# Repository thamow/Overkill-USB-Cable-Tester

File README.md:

# Overkill USB Cable Tester

[Post on Reddit](https://www.reddit.com/r/PCB/comments/1lwca66/review_request_overkill_usb_tester/?utm_source=share&utm_medium=web3x&utm_name=web3xcss&utm_term=1&utm_content=share_button)

Disclaimer: Work in Progress! Do not expect the current version to work as intended!

**tl;dr:** Designed my second ever PCB and want some suggestions for potential improvements or problems / errors in my design (PCB not routed yet). See questions down below (last paragraph).

Yes, this design is complete overkill! This PCB is mostly for me to try stuff out and intentionally not cost-optimised. That said, should you see improvements without reducing the feature set, go ahead!

## Questions

Some of my most pressing questions are:

- **Will the LED Matrix work** with the two SN74HC595s? (see paragraph "Indicator LED Matrix" below)
- **How does the double mapping of Pin PA14 work?** (BOOT0 & SWCLK) What do I have to do in order to use it in either function? (-> paragraph "SWD" below)
- **Does the back-feed protection work the way I intend it to?** (-> paragraph "Power" below)
- **Is there something I should have done differently regarding the USB-C of the UART controller?** Anything wrong with the ESD protection or shield filtering I put there? (see schematic image 3)
- **Do I need series resistors on the SWD lines?** They are supposed to act as noise suppression to reduce ringing and stuff. Are they good to have or unnecessary? (see R10, R11, R12)

Again, I know the design is complete overkill but suggestions for more elegant solutions are more than welcome!

## Detailed Info

I wanted to have a USB Tester for a long time and thought instead of buying one I'd seize the opportunity to learn some things about PCB design and USB-C. As stated above, this is my second ever PCB design and I originally have a background in IT not EE so expect some rookie mistakes! What started out as a simple "put current through to light some LEDs" turned into "i definitely want cross wire and short detection and want to read out eMarkers and everything".

### Basic working principle

I have two sides: Side A (left side) and Side B (right side). If you plug in a cable (one end into each side) the tester should check which pins are connected and which aren't, which are connected even though they shouldn't and so on. I do this by applying a voltage to each pin after another on the A-Side (s. Output Drivers SN74HC595) and checking which pins get pulled high on the opposing Side B (s. Input Drivers SN74HC165).

#### Detailed working principle

Below I will go into detail on the individual sections of the schematic and my reasoning behind some things.

#### µC - STM32

The controller IC is an STM32 G071CBT6.

##### USB PD

I chose that controller specifically due to its build-in USB PD Communication Chip. I want to use it to read out the eMarkers of USB C Cables to be able to check the cables current and speed rating and potential USB Alt modes.

You may notice that I put the CC1 and CC2 lines of both side on a separate USB PD Controller as well as on ADC pins (12-15). I did this so that i could check for built-in pull-up and pull-down resistors inside the cable (which some cables must include in order to be up to spec).

##### Programming

To program the µC I implemented two methods: UART and SWD.

**SWD**

SWD itself seems to be quite simple from my understanding. I broke out the necessary pins to an appropriate connector (J1). The information I found only does however raise some questions regarding series resistors (see questions section down below).

Furthermore, the STM32 I choose uses the SWCLK pin as the BOOT0 pin as well (Alternate Mode). I could not yet find out how that is supposed to work. Therefore I opted to place a jumper (JP7) to either connect to the BOOT push button (SW4) or to the SWD connector (J1).

**UART**

Because I wanted to try it out, in addition to the SWD interface I used a serial to USB converter (U3 CH340X) to program the µC via USB and to be able to implement serial log to a PC for more detailed test reports.

Again, it was not clear to me how to connect the RST and BOOT0 pins exactly so I placed two solder jumper (JP5/6) to be able to easily change the pin mapping while testing.

#### Indicator LED Matrix

Well...the number of LEDs got a bit out of hand... So I decided to use a matrix powered by two SN74HC595 tri-state shift registers. Partly I did this to limit the number of shift registers needed but partly because I wanted to try it, which seems to be the theme of this build.

#### Power

With the external SWD and USB inputs I expanded the power circuit (which is probably a good thing should the CR2032 prove to be insufficient). The power circuit is designed around a buck converter to step down the external supply voltage (5V USB) down to 3.3V.

Since the µC will happily run with less then 2.5V so the voltage drop that will occur when feeding the buck converter with 3.3V from the SWD interface should be a non-issue but if the buck converter fail, I can still bridge that (JP3) and feed the board directly.

I implemented back-feed protection so that if external power is provided, it does not apply a potentially higher positive voltage to the battery and cuts it off. Here I wanted to avoid a voltage drop of 300mV so I used a MOSFET instead.

#### Test Points

I had that idea about the board design you can see in the images. To pull that off I designed a custom multi-part symbol and footprint.

In the fourth image you can see that I labeled the different test-points. Essentially the PCB Design doubles as test points. Each pin of the USB-C graphic in the centre of the PCB is a test point for that appropriate pin. Since each pin exists on both sides but the graphics only provides one pad per pin, I added a second test point for each pin. For example, if you would want to test for continuity between Pin B12 (upmost left pin) with a multimeter, you would test between the upper left test point left from GND label and the B12 pin inside the graphics.

Again, I tried to show this in the fourth image I hope that makes it more clear.

#### Unpopulated Parts

You may have noticed some unpopulated parts on my PCB. In the case of pull-up or down resistors those are mainly there as placeholders in case I need them but according to the datasheets I shouldn't need them.

The series resistors on the SWD lines are supposed to be noise suppression resistors? I am quite unsure if they are necessary (see question in the questions section).

And that's about it I guess!

## Improvements for the next Revision

### STM32 with USB 2.0 build in

To replace the external UART Bridge that presents a COM port for programming via USB and for serial out, a different MCU could be used with built-in USB 2.0 support instead. This has multiple advantages:

- reducing number of parts (smaller BOM)
  
- broader feature set (debugging/virtual network adapter via USB, which could be used for running a web server hosting a website https://github.com/fetisov/lrndis, https://www.youtube.com/watch?v=hsqWIqY8b6A), (it also makes web flashing possible through WebUSB https://github.com/siliconwitchery/web-stm32-updater), (of course, serial communication is also an option via CDC https://wiki.st.com/stm32mcu/wiki/Introduction_to_USB_with_STM32)

The STM32G0 series seems the be the best suited one, as it features two USB-C PD interfaces (UCPD1/2). These are used for checking for eMarkers on both USB-C receptacles (Side A and B). One could argue that only one UCPD interface is needed since eMarkers can be read out from either side of the cable. For USB-C to C and also USB-C to A cables this would work fine. The UCPD interface would be connected to the B-Side receptacle and read out any eMarker in the cable (A-Side would not work for USB-C to A cables, which are Plugged in to the B-Side Type C receptacle, not the A-Side one).

For cables like USB-C to Micro-B this would however not work.

## License

This project is licensed under the

[Creative Commons Attribution-NonCommercial-ShareAlike 4.0 International License](https://creativecommons.org/licenses/by-nc-sa/4.0/).

Copyright (c) 2025 by the original creator and author (GitHub: [thamow](https://github.com/thamow))

Attribution required. Commercial use not permitted. Derivatives must be shared under the same license.

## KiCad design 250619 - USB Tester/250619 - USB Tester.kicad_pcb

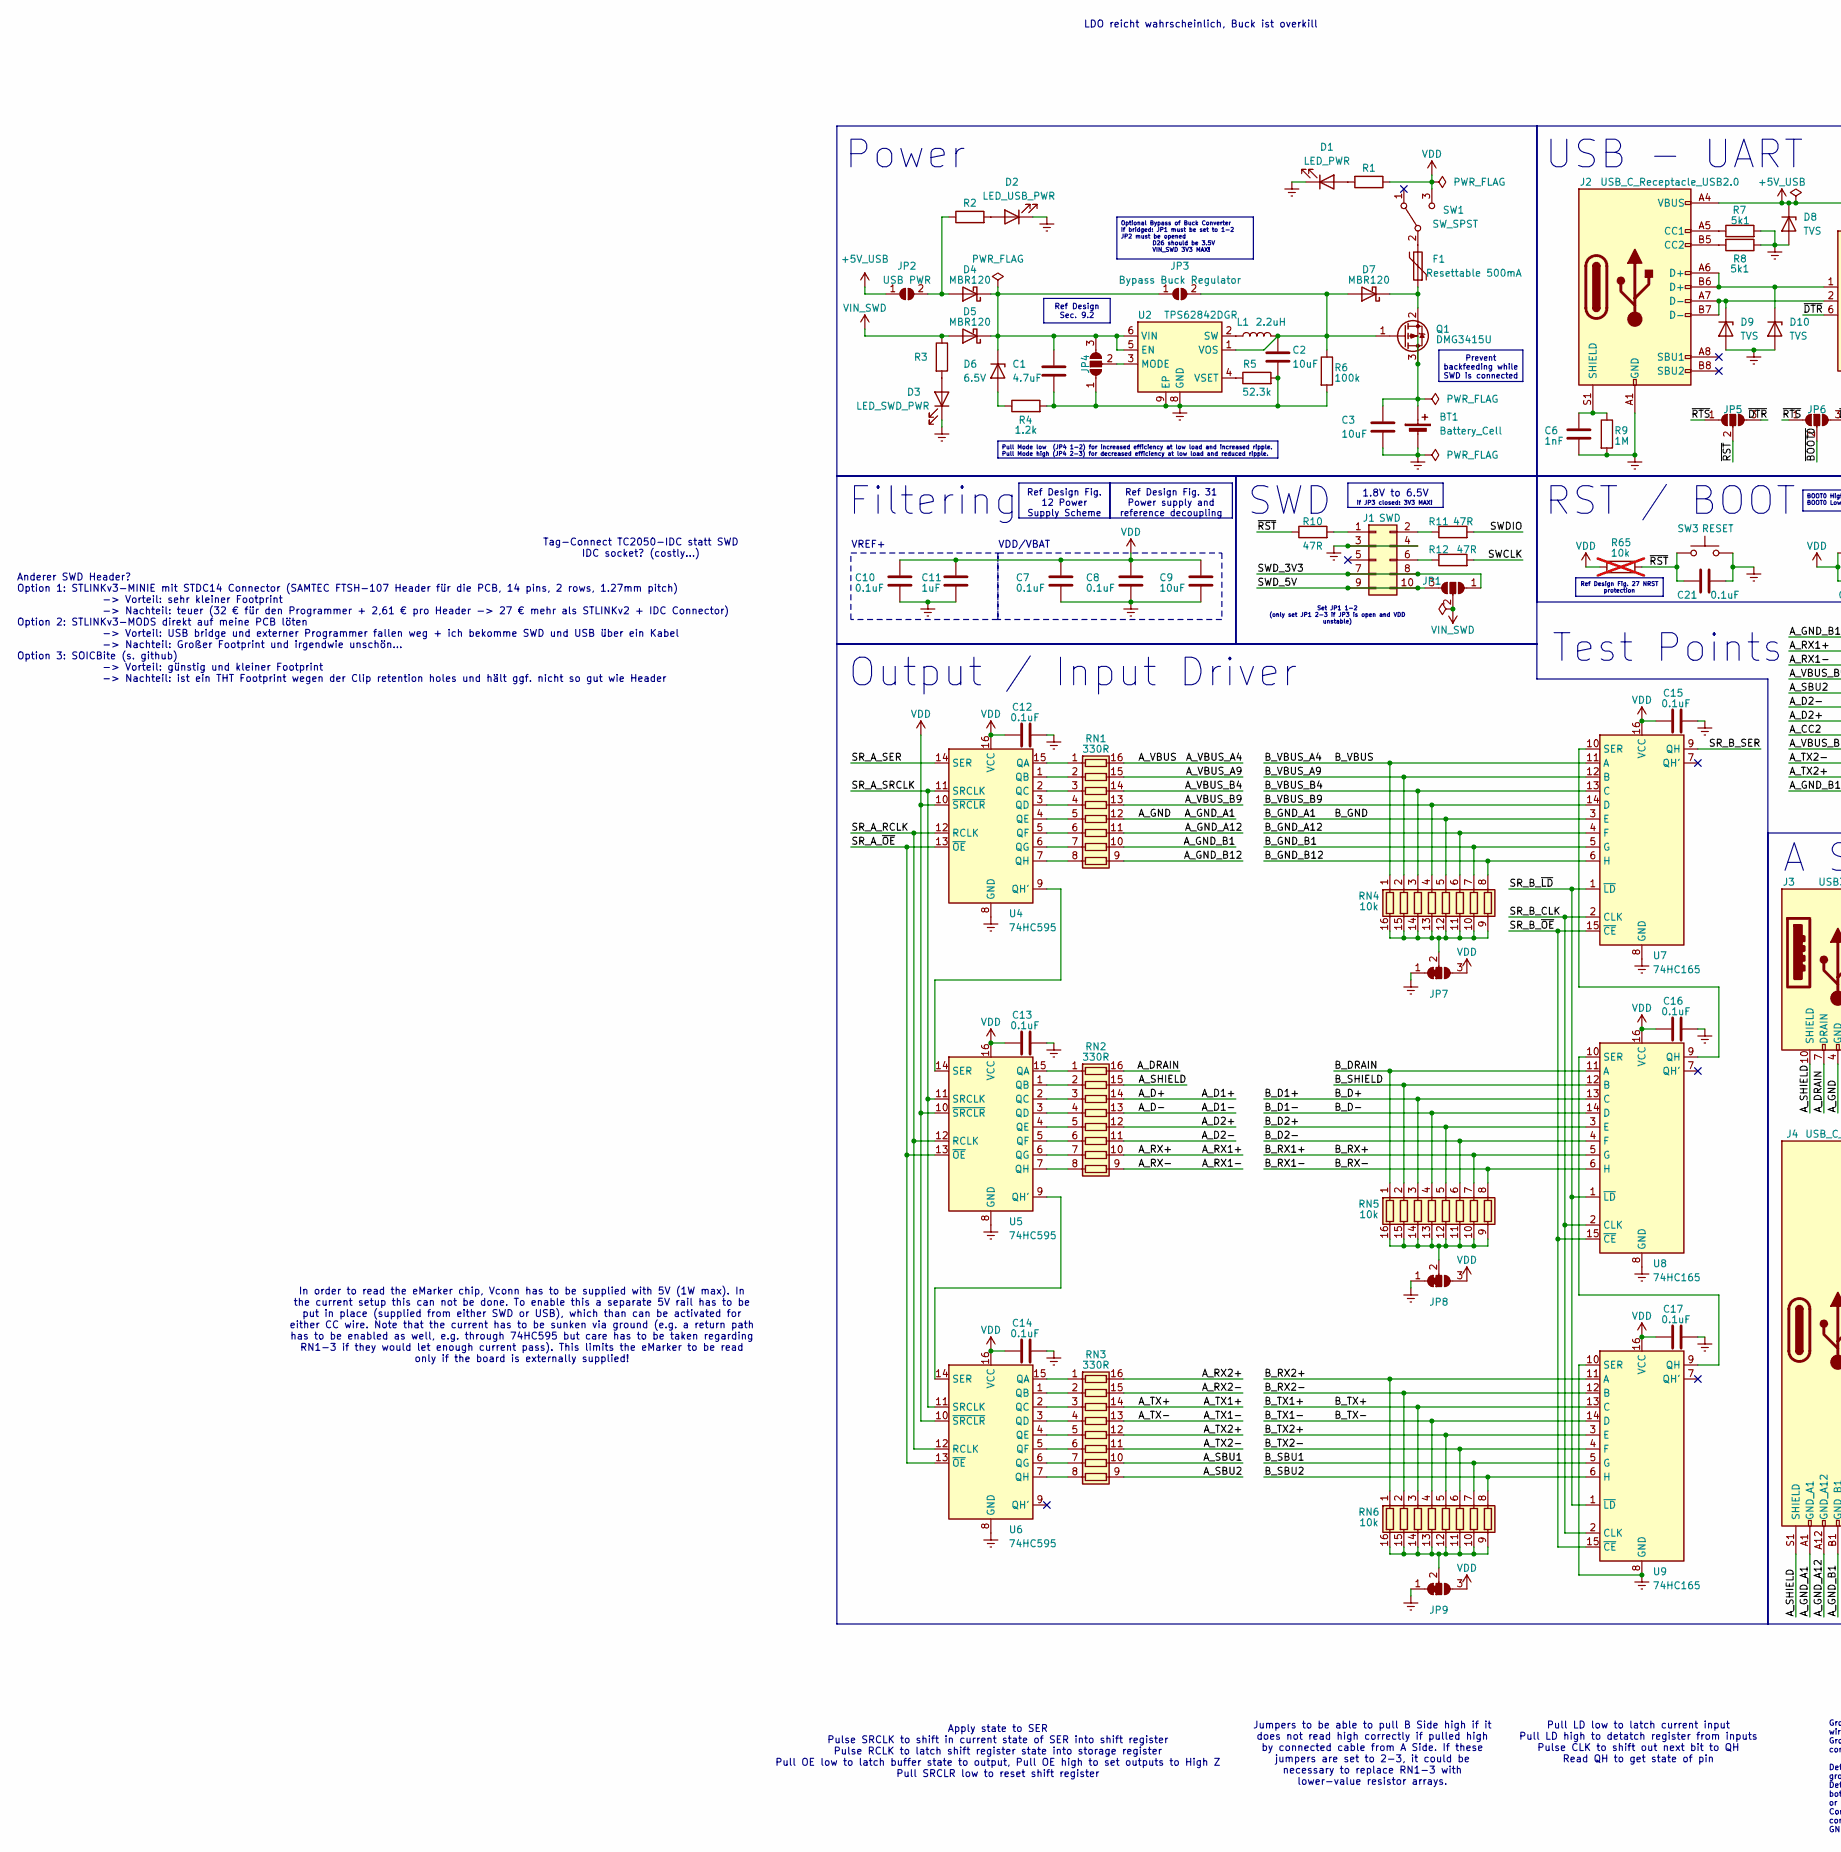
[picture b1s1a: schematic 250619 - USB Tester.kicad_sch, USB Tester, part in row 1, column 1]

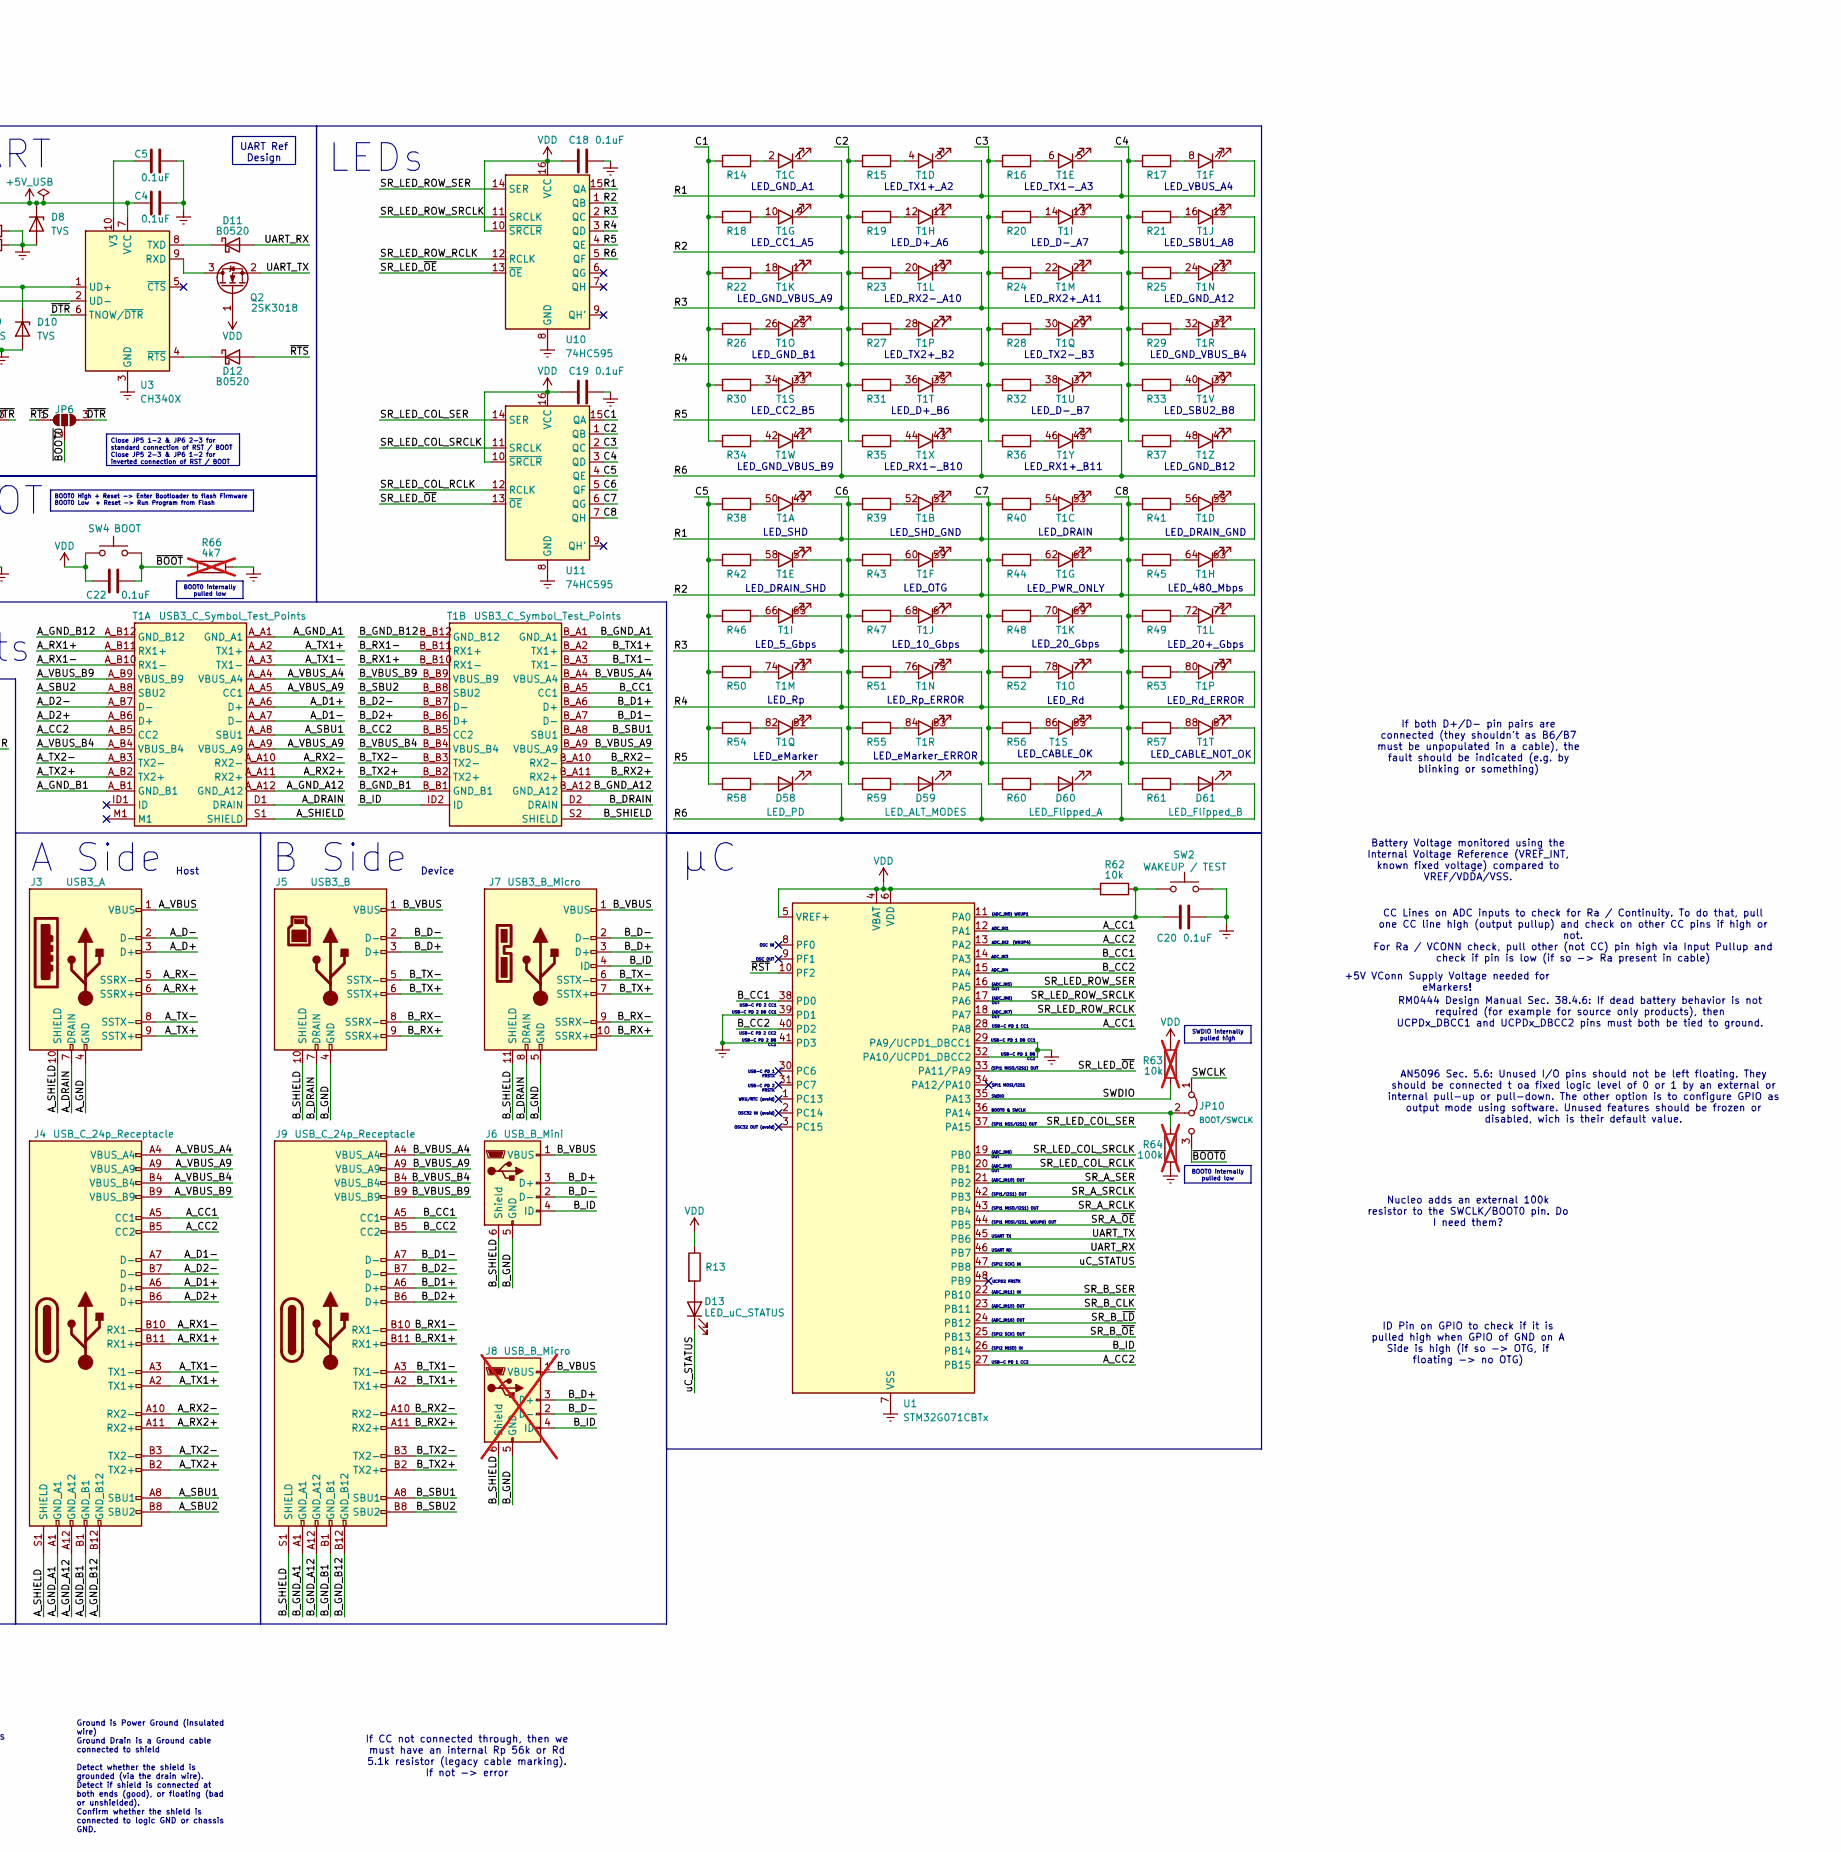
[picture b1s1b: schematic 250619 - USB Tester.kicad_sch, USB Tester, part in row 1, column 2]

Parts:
BT1: Battery_Cell; BatteryHolder_Keystone_1060_1x2032_BP; LCSC Part # C964775
C1: 4.7uF; C_0805_2012Metric; LCSC Part # C335105
C2: 10uF; C_0805_2012Metric; LCSC Part # C162167
C3, C9: 10uF; C_0805_2012Metric
C4, C5, C7, C8, C10, C12, C13, C14, C15, C16, C17, C18, C19, C20, C21, C22: 0.1uF; C_0805_2012Metric
C6: 1nF; C_0805_2012Metric
C11: 1uF; C_0805_2012Metric
D1: LED_PWR; LED_0805_2012Metric_Pad1.15x1.40mm_HandSolder_Minimal
D2: LED_USB_PWR; LED_0805_2012Metric_Pad1.15x1.40mm_HandSolder_Minimal
D3: LED_SWD_PWR; LED_0805_2012Metric_Pad1.15x1.40mm_HandSolder_Minimal
D4, D5, D7: MBR120; D_SOD-123FL; LCSC Part # C223608
D6: 6.5V; D_SOD-123; LCSC Part # C47283689
D8, D9, D10: TVS; D_SOD-923; LCSC Part # C896236
D11, D12: B0520; D_SOD-123; LCSC Part # C7502707
D13: LED_uC_STATUS; LED_0805_2012Metric_Pad1.15x1.40mm_HandSolder_Minimal
D58: LED_PD; LED_0805_2012Metric_Pad1.15x1.40mm_HandSolder_Minimal
D59: LED_ALT_MODES; LED_0805_2012Metric_Pad1.15x1.40mm_HandSolder_Minimal
D60: LED_Flipped_A; LED_0805_2012Metric_Pad1.15x1.40mm_HandSolder_Minimal
D61: LED_Flipped_B; LED_0805_2012Metric_Pad1.15x1.40mm_HandSolder_Minimal
F1: Resettable 500mA; Fuse_0805_2012Metric; LCSC Part # C2760262
J1: SWD; IDC-Header_2x05_P2.54mm_Vertical_SMD
J2: USB_C_Receptacle_USB2.0; USB_C_Receptacle_GCT_USB4105-xx-A_16P_TopMnt_Horizontal
J3: USB3_A; USB3_A_Receptacle
J4, J9: USB_C_24p_Receptacle; USB_C_Receptacle_24P
J5: USB3_B; USB3_B_Receptacle
J6: USB_B_Mini; USB_Mini-B_Wuerth_65100516121_Horizontal
J7: USB3_B_Micro; USB3_Micro-B_Hirose_ZX360D-B-10P
J8: USB_B_Micro; USB_Micro-B_Amphenol_10118194_Horizontal; not fitted
JP1, JP4, JP5, JP6: SolderJumper_3_Open; SolderJumper-3_P1.3mm_Open_RoundedPad1.0x1.5mm_NumberLabels
JP2: USB PWR; SolderJumper-2_P1.3mm_Open_RoundedPad1.0x1.5mm
JP3: Bypass Buck Regulator; SolderJumper-2_P1.3mm_Open_RoundedPad1.0x1.5mm
JP7, JP8, JP9: SolderJumper_3_Bridged12; SolderJumper-3_P1.3mm_Bridged2Bar12_RoundedPad1.0x1.5mm_Num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
JP10: BOOT/SWCLK; PinHeader_1x03_P2.54mm_Horizontal_SMD
L1: 2.2uH; L_0805_2012Metric; LCSC Part # C2049745
Q1: DMG3415U; SOT-23; LCSC Part # C7202986
Q2: 2SK3018; SOT-23; LCSC Part # C181084
R1, R2, R3, R13, R14, R15, R16, R17, R18, R19, R20, R21, R22, R23, R24, R25, R26, R27, R28, R29, R30, R31, R32, R33, R34, R35, R36, R37, R38, R39, R40, R41, R42, R43, R44, R45, R46, R47, R48, R49, R50, R51, R52, R53, R54, R55, R56, R57, R58, R59, R60, R61: R; R_0805_2012Metric
R4: 1.2k; R_0805_2012Metric
R5: 52.3k; R_0805_2012Metric; LCSC Part # C2933465
R6: 100k; R_0805_2012Metric; LCSC Part # C149504
R7, R8: 5k1; R_0805_2012Metric
R9: 1M; R_0805_2012Metric
R10, R11, R12: 47R; R_0805_2012Metric
R62: 10k; R_0805_2012Metric
R63, R65: 10k; R_0805_2012Metric; not fitted
R64: 100k; R_0805_2012Metric; not fitted
R66: 4k7; R_0805_2012Metric; not fitted
RN1, RN2, RN3: 330R; R_Array_Convex_8x0402_YC248
RN4, RN5, RN6: 10k; R_Array_Convex_8x0402_YC248
SW1: SW_SPST; SW_SPDT_PCM12; LCSC Part # C22448006
SW2: WAKEUP / TEST; SW_Push_SPST_SL; LCSC Part # C720477
SW3: RESET; SW_Push_SPST_SL; LCSC Part # C720477
SW4: BOOT; SW_Push_SPST_SL; LCSC Part # C720477
T1: USB3_C_Symbol_Test_Points
U1: STM32G071CBTx; LQFP-48_7x7mm_P0.5mm
U2: TPS62842DGR; HVSSOP-8-1EP_3x3mm_P0.65mm_EP1.57x1.89mm
U3: CH340X; MSOP-10_3x3mm_P0.5mm
U4, U5, U6, U10, U11: 74HC595; SOIC-16_4.55x10.3mm_P1.27mm; LCSC Part # C10092
U7, U8, U9: 74HC165; SOIC-16_4.55x10.3mm_P1.27mm; LCSC Part # C61060

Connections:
+5V_USB: C4.2, D8.1 (K), J2.A4 (VBUS), J2.A9 (VBUS), J2.B4 (VBUS), J2.B9 (VBUS), JP2.1 (A), U3.7 (VCC)
/A_CC1: J4.A5 (CC1), U1.12 (PA1), U1.28 (PA8)
/A_CC2: J4.B5 (CC2), T1.A_B5 (CC2), U1.13 (PA2), U1.27 (PB15)
/A_D2+: J4.B6 (D+), RN2.12 (R5.2), T1.A_B6 (D+)
/A_D2-: J4.B7 (D-), RN2.11 (R6.2), T1.A_B7 (D-)
/A_D+: J3.3 (D+), J4.A6 (D+), RN2.14 (R3.2), T1.A_A6 (D+)
/A_D-: J3.2 (D-), J4.A7 (D-), RN2.13 (R4.2), T1.A_A7 (D-)
/A_DRAIN: J3.7 (DRAIN), RN2.16 (R1.2), T1.D1 (DRAIN)
/A_GND: J3.4 (GND), J4.A1 (GND_A1), RN1.12 (R5.2), T1.A_A1 (GND_A1)
/A_GND_A12: J4.A12 (GND_A12), RN1.11 (R6.2), T1.A_A12 (GND_A12)
/A_GND_B1: J4.B1 (GND_B1), RN1.10 (R7.2), T1.A_B1 (GND_B1)
/A_GND_B12: J4.B12 (GND_B12), RN1.9 (R8.2), T1.A_B12 (GND_B12)
/A_RX2+: J4.A11 (RX2+), RN3.16 (R1.2), T1.A_A11 (RX2+)
/A_RX2-: J4.A10 (RX2-), RN3.15 (R2.2), T1.A_A10 (RX2-)
/A_RX+: J3.6 (SSRX+), J4.B11 (RX1+), RN2.10 (R7.2), T1.A_B11 (RX1+)
/A_RX-: J3.5 (SSRX-), J4.B10 (RX1-), RN2.9 (R8.2), T1.A_B10 (RX1-)
/A_SBU1: J4.A8 (SBU1), RN3.10 (R7.2), T1.A_A8 (SBU1)
/A_SBU2: J4.B8 (SBU2), RN3.9 (R8.2), T1.A_B8 (SBU2)
/A_SHIELD: J3.10 (SHIELD), J4.S1 (SHIELD), RN2.15 (R2.2), T1.S1 (SHIELD)
/A_TX2+: J4.B2 (TX2+), RN3.12 (R5.2), T1.A_B2 (TX2+)
/A_TX2-: J4.B3 (TX2-), RN3.11 (R6.2), T1.A_B3 (TX2-)
/A_TX+: J3.9 (SSTX+), J4.A2 (TX1+), RN3.14 (R3.2), T1.A_A2 (TX1+)
/A_TX-: J3.8 (SSTX-), J4.A3 (TX1-), RN3.13 (R4.2), T1.A_A3 (TX1-)
/A_VBUS: J3.1 (VBUS), J4.A4 (VBUS_A4), RN1.16 (R1.2), T1.A_A4 (VBUS_A4)
/A_VBUS_A9: J4.A9 (VBUS_A9), RN1.15 (R2.2), T1.A_A5 (CC1), T1.A_A9 (VBUS_A9)
/A_VBUS_B4: J4.B4 (VBUS_B4), RN1.14 (R3.2), T1.A_B4 (VBUS_B4)
/A_VBUS_B9: J4.B9 (VBUS_B9), RN1.13 (R4.2), T1.A_B9 (VBUS_B9)
/B_CC1: J9.A5 (CC1), T1.B_A5 (CC1), U1.14 (PA3), U1.38 (PD0)
/B_CC2: J9.B5 (CC2), T1.B_B5 (CC2), U1.15 (PA4), U1.40 (PD2)
/B_D2+: J9.B6 (D+), RN5.5 (R5.1), T1.B_B6 (D+), U8.3 (E)
/B_D2-: J9.B7 (D-), RN5.6 (R6.1), T1.B_B7 (D-), U8.4 (F)
/B_D+: J5.3 (D+), J6.3 (D+), J7.3 (D+), J8.3 (D+), J9.A6 (D+), RN5.3 (R3.1), T1.B_A6 (D+), U8.13 (C)
/B_D-: J5.2 (D-), J6.2 (D-), J7.2 (D-), J8.2 (D-), J9.A7 (D-), RN5.4 (R4.1), T1.B_A7 (D-), U8.14 (D)
/B_DRAIN: J5.7 (DRAIN), J7.8 (DRAIN), RN5.1 (R1.1), T1.D2 (DRAIN), U8.11 (A)
/B_GND: J5.4 (GND), J6.5 (GND), J7.5 (GND), J8.5 (GND), J9.A1 (GND_A1), RN4.5 (R5.1), T1.B_A1 (GND_A1), U7.3 (E)
/B_GND_A12: J9.A12 (GND_A12), RN4.6 (R6.1), T1.B_A12 (GND_A12), U7.4 (F)
/B_GND_B1: J9.B1 (GND_B1), RN4.7 (R7.1), T1.B_B1 (GND_B1), U7.5 (G)
/B_GND_B12: J9.B12 (GND_B12), RN4.8 (R8.1), T1.B_B12 (GND_B12), U7.6 (H)
/B_ID: J6.4 (ID), J7.4 (ID), J8.4 (ID), T1.ID2 (ID), U1.26 (PB14)
/B_RX2+: J9.A11 (RX2+), RN6.1 (R1.1), T1.B_A11 (RX2+), U9.11 (A)
/B_RX2-: J9.A10 (RX2-), RN6.2 (R2.1), T1.B_A10 (RX2-), U9.12 (B)
/B_RX+: J5.9 (SSRX+), J7.10 (SSRX+), J9.B11 (RX1+), RN5.7 (R7.1), T1.B_B10 (RX1-), U8.5 (G)
/B_RX-: J5.8 (SSRX-), J7.9 (SSRX-), J9.B10 (RX1-), RN5.8 (R8.1), T1.B_B11 (RX1+), U8.6 (H)
/B_SBU1: J9.A8 (SBU1), RN6.7 (R7.1), T1.B_A8 (SBU1), U9.5 (G)
/B_SBU2: J9.B8 (SBU2), RN6.8 (R8.1), T1.B_B8 (SBU2), U9.6 (H)
/B_SHIELD: J5.10 (SHIELD), J6.6 (Shield), J7.11 (SHIELD), J8.6 (Shield), J9.S1 (SHIELD), RN5.2 (R2.1), T1.S2 (SHIELD), U8.12 (B)
/B_TX2+: J9.B2 (TX2+), RN6.5 (R5.1), T1.B_B2 (TX2+), U9.3 (E)
/B_TX2-: J9.B3 (TX2-), RN6.6 (R6.1), T1.B_B3 (TX2-), U9.4 (F)
/B_TX+: J5.6 (SSTX+), J7.7 (SSTX+), J9.A2 (TX1+), RN6.3 (R3.1), T1.B_A2 (TX1+), U9.13 (C)
/B_TX-: J5.5 (SSTX-), J7.6 (SSTX-), J9.A3 (TX1-), RN6.4 (R4.1), T1.B_A3 (TX1-), U9.14 (D)
/B_VBUS: J5.1 (VBUS), J6.1 (VBUS), J7.1 (VBUS), J8.1 (VBUS), J9.A4 (VBUS_A4), RN4.1 (R1.1), T1.B_A4 (VBUS_A4), U7.11 (A)
/B_VBUS_A9: J9.A9 (VBUS_A9), RN4.2 (R2.1), T1.B_A9 (VBUS_A9), U7.12 (B)
/B_VBUS_B4: J9.B4 (VBUS_B4), RN4.3 (R3.1), T1.B_B4 (VBUS_B4), U7.13 (C)
/B_VBUS_B9: J9.B9 (VBUS_B9), RN4.4 (R4.1), T1.B_B9 (VBUS_B9), U7.14 (D)
/C1: R14.1, R18.1, R22.1, R26.1, R30.1, R34.1, U11.15 (QA)
/C2: R15.1, R19.1, R23.1, R27.1, R31.1, R35.1, U11.1 (QB)
/C3: R16.1, R20.1, R24.1, R28.1, R32.1, R36.1, U11.2 (QC)
/C4: R17.1, R21.1, R25.1, R29.1, R33.1, R37.1, U11.3 (QD)
/C5: R38.1, R42.1, R46.1, R50.1, R54.1, R58.1, U11.4 (QE)
/C6: R39.1, R43.1, R47.1, R51.1, R55.1, R59.1, U11.5 (QF)
/C7: R40.1, R44.1, R48.1, R52.1, R56.1, R60.1, U11.6 (QG)
/C8: R41.1, R45.1, R49.1, R53.1, R57.1, R61.1, U11.7 (QH)
/R1: T1.1, T1.3, T1.5, T1.7, T1.49, T1.51, T1.53, T1.55, U10.15 (QA)
/R2: T1.9, T1.11, T1.13, T1.15, T1.57, T1.59, T1.61, T1.63, U10.1 (QB)
/R3: T1.17, T1.19, T1.21, T1.23, T1.65, T1.67, T1.69, T1.71, U10.2 (QC)
/R4: T1.25, T1.27, T1.29, T1.31, T1.73, T1.75, T1.77, T1.79, U10.3 (QD)
/R5: T1.33, T1.35, T1.37, T1.39, T1.81, T1.83, T1.85, T1.87, U10.4 (QE)
/R6: D58.1 (K), D59.1 (K), D60.1 (K), D61.1 (K), T1.41, T1.43, T1.45, T1.47, U10.5 (QF)
/SR_A_RCLK: U1.43 (PB4), U4.12 (RCLK), U5.12 (RCLK), U6.12 (RCLK)
/SR_A_SER: U1.21 (PB2), U4.14 (SER)
/SR_A_SRCLK: U1.42 (PB3), U4.11 (SRCLK), U5.11 (SRCLK), U6.11 (SRCLK)
/SR_A_~OE: U1.44 (PB5), U4.13 (~OE), U5.13 (~OE), U6.13 (~OE)
/SR_B_CLK: U1.23 (PB11), U7.2 (CLK), U8.2 (CLK), U9.2 (CLK)
/SR_B_SER: U1.22 (PB10), U7.9 (QH)
/SR_B_~LD: U1.24 (PB12), U7.1 (~LD), U8.1 (~LD), U9.1 (~LD)
/SR_B_~OE: U1.25 (PB13), U7.15 (~CE), U8.15 (~CE), U9.15 (~CE)
/SR_LED_COL_RCLK: U1.20 (PB1), U11.12 (RCLK)
/SR_LED_COL_SER: U1.37 (PA15), U11.14 (SER)
/SR_LED_COL_SRCLK: U1.19 (PB0), U11.11 (SRCLK)
/SR_LED_ROW_RCLK: U1.18 (PA7), U10.12 (RCLK)
/SR_LED_ROW_SER: U1.16 (PA5), U10.14 (SER)
/SR_LED_ROW_SRCLK: U1.17 (PA6), U10.11 (SRCLK)
/SR_LED_~OE: U1.33 (PA11/PA9), U10.13 (~OE), U11.13 (~OE)
/SWCLK: JP10.1 (A), R12.2
/SWDIO: R11.2, R63.2, U1.35 (PA13)
/SWD_3V3: J1.7, J1.8, JP1.1 (A)
/SWD_5V: J1.9, J1.10, JP1.3 (B)
/UART_RX: D11.2 (A), U1.46 (PB7)
/UART_TX: Q2.2 (S), U1.45 (PB6)
/uC_STATUS: D13.1 (K), U1.47 (PB8)
/~BOOT0: JP6.2 (C), JP10.3 (B)
/~BOOT: C22.2, R66.2, SW4.1
/~DTR: JP5.3 (B), JP6.3 (B), U3.6 (TNOW/~DTR)
/~RST: C21.2, JP5.2 (C), R10.1, R65.1, SW3.1, U1.10 (PF2)
/~RTS: D12.2 (A), JP5.1 (A), JP6.1 (A)
GNDREF: BT1.2 (-), C1.2, C2.2, C3.1, C4.1, C5.1, C6.2, C7.1, C8.1, C9.1, C10.1, C11.1, C12.1, C13.1, C14.1, C15.1, C16.1, C17.1, C18.1, C19.1, C20.1, C21.1, D1.1 (K), D2.1 (K), D3.1 (K), D8.2 (A), D9.2 (A), D10.2 (A), J1.3, J1.4, J2.A1 (GND), J2.A12 (GND), J2.B1 (GND), J2.B12 (GND), JP4.1 (A), JP7.1 (A), JP8.1 (A), JP9.1 (A), R4.2, R5.2, R6.2, R7.2, R8.1, R9.2, R64.2, R66.1, SW2.2, SW3.2, U1.7 (VSS), U1.29 (PA9/UCPD1_DBCC1), U1.32 (PA10/UCPD1_DBCC2), U1.39 (PD1), U1.41 (PD3), U2.8 (GND), U2.9 (EP), U3.3 (GND), U4.8 (GND), U5.8 (GND), U6.8 (GND), U7.8 (GND), U8.8 (GND), U9.8 (GND), U9.10 (SER), U10.8 (GND), U11.8 (GND)
unnamed: BT1.1 (+), C3.2, Q1.3 (D)
unnamed: D1.2 (A), R1.2
unnamed: D2.2 (A), R2.2
unnamed: D3.2 (A), R3.2
unnamed: D4.2 (A), JP2.2 (B), R2.1
unnamed: C1.1, D4.1 (K), D5.1 (K), D6.1 (K), JP3.1 (A), JP4.3 (B), U2.5 (EN), U2.6 (VIN)
unnamed: D6.2 (A), R4.1
unnamed: C2.1, D7.2 (A), JP3.2 (B), L1.2, Q1.1 (G), R6.1, U2.1 (VOS)
unnamed: D7.1 (K), F1.1, Q1.2 (S)
unnamed: D9.1 (K), J2.A7 (D-), J2.B7 (D-), U3.2 (UD-)
unnamed: D10.1 (K), J2.A6 (D+), J2.B6 (D+), U3.1 (UD+)
unnamed: D11.1 (K), U3.8 (TXD)
unnamed: D12.1 (K), U3.4 (~RTS)
unnamed: D13.2 (A), R13.2
unnamed: D58.2 (A), R58.2
unnamed: D59.2 (A), R59.2
unnamed: D60.2 (A), R60.2
unnamed: D61.2 (A), R61.2
unnamed: J1.1, R10.2
unnamed: J1.2, R11.1
unnamed: J1.6, R12.1
unnamed: J2.A5 (CC1), R7.1
unnamed: J2.B5 (CC2), R8.2
unnamed: C6.1, J2.S1 (SHIELD), R9.1
unnamed: JP4.2 (C), U2.3 (MODE)
unnamed: JP7.2 (C), RN4.9 (R8.2), RN4.10 (R7.2), RN4.11 (R6.2), RN4.12 (R5.2), RN4.13 (R4.2), RN4.14 (R3.2), RN4.15 (R2.2), RN4.16 (R1.2)
unnamed: JP8.2 (C), RN5.9 (R8.2), RN5.10 (R7.2), RN5.11 (R6.2), RN5.12 (R5.2), RN5.13 (R4.2), RN5.14 (R3.2), RN5.15 (R2.2), RN5.16 (R1.2)
unnamed: JP9.2 (C), RN6.9 (R8.2), RN6.10 (R7.2), RN6.11 (R6.2), RN6.12 (R5.2), RN6.13 (R4.2), RN6.14 (R3.2), RN6.15 (R2.2), RN6.16 (R1.2)
unnamed: JP10.2 (C), R64.1, U1.36 (PA14)
unnamed: Q2.3 (D), U3.9 (RXD)
unnamed: R14.2, T1.2
unnamed: R15.2, T1.4
unnamed: R16.2, T1.6
unnamed: R17.2, T1.8
unnamed: R18.2, T1.10
unnamed: R19.2, T1.12
unnamed: R20.2, T1.14
unnamed: R21.2, T1.16
unnamed: R22.2, T1.18
unnamed: R23.2, T1.20
unnamed: R24.2, T1.22
unnamed: R25.2, T1.24
unnamed: R26.2, T1.26
unnamed: R27.2, T1.28
unnamed: R28.2, T1.30
unnamed: R29.2, T1.32
unnamed: R30.2, T1.34
unnamed: R31.2, T1.36
unnamed: R32.2, T1.38
unnamed: R33.2, T1.40
unnamed: R34.2, T1.42
unnamed: R35.2, T1.44
unnamed: R36.2, T1.46
unnamed: R37.2, T1.48
unnamed: R38.2, T1.50
unnamed: R39.2, T1.52
unnamed: R40.2, T1.54
unnamed: R41.2, T1.56
unnamed: R42.2, T1.58
unnamed: R43.2, T1.60
unnamed: R44.2, T1.62
unnamed: R45.2, T1.64
unnamed: R46.2, T1.66
unnamed: R47.2, T1.68
unnamed: R48.2, T1.70
unnamed: R49.2, T1.72
unnamed: R50.2, T1.74
unnamed: R51.2, T1.76
unnamed: R52.2, T1.78
unnamed: R53.2, T1.80
unnamed: R54.2, T1.82
unnamed: R55.2, T1.84
unnamed: R56.2, T1.86
unnamed: R57.2, T1.88
unnamed: RN1.1 (R1.1), U4.15 (QA)
unnamed: RN1.2 (R2.1), U4.1 (QB)
unnamed: RN1.3 (R3.1), U4.2 (QC)
unnamed: RN1.4 (R4.1), U4.3 (QD)
unnamed: RN1.5 (R5.1), U4.4 (QE)
unnamed: RN1.6 (R6.1), U4.5 (QF)
unnamed: RN1.7 (R7.1), U4.6 (QG)
unnamed: RN1.8 (R8.1), U4.7 (QH)
unnamed: RN2.1 (R1.1), U5.15 (QA)
unnamed: RN2.2 (R2.1), U5.1 (QB)
unnamed: RN2.3 (R3.1), U5.2 (QC)
unnamed: RN2.4 (R4.1), U5.3 (QD)
unnamed: RN2.5 (R5.1), U5.4 (QE)
unnamed: RN2.6 (R6.1), U5.5 (QF)
unnamed: RN2.7 (R7.1), U5.6 (QG)
unnamed: RN2.8 (R8.1), U5.7 (QH)
unnamed: RN3.1 (R1.1), U6.15 (QA)
unnamed: RN3.2 (R2.1), U6.1 (QB)
unnamed: RN3.3 (R3.1), U6.2 (QC)
unnamed: RN3.4 (R4.1), U6.3 (QD)
unnamed: RN3.5 (R5.1), U6.4 (QE)
unnamed: RN3.6 (R6.1), U6.5 (QF)
unnamed: RN3.7 (R7.1), U6.6 (QG)
unnamed: RN3.8 (R8.1), U6.7 (QH)
unnamed: F1.2, SW1.2 (B)
unnamed: C20.2, R62.1, SW2.1, U1.11 (PA0)
unnamed: L1.1, U2.2 (SW)
unnamed: R5.1, U2.4 (VSET)
unnamed: C5.2, U3.10 (V3)
unnamed: U4.9 (QH'), U5.14 (SER)
unnamed: U5.9 (QH'), U6.14 (SER)
unnamed: U7.10 (SER), U8.9 (QH)
unnamed: U8.10 (SER), U9.9 (QH)
VDD: C7.2, C8.2, C9.2, C10.2, C11.2, C12.2, C13.2, C14.2, C15.2, C16.2, C17.2, C18.2, C19.2, C22.1, JP7.3 (B), JP8.3 (B), JP9.3 (B), Q2.1 (G), R1.1, R13.1, R62.2, R63.1, R65.2, SW1.3 (C), SW4.2, U1.4 (VBAT), U1.5 (VREF+), U1.6 (VDD), U4.10 (~SRCLR), U4.16 (VCC), U5.10 (~SRCLR), U5.16 (VCC), U6.10 (~SRCLR), U6.16 (VCC), U7.16 (VCC), U8.16 (VCC), U9.16 (VCC), U10.10 (~SRCLR), U10.16 (VCC), U11.10 (~SRCLR), U11.16 (VCC)
VIN_SWD: D5.2 (A), JP1.2 (C), R3.1

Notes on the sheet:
+5V VConn Supply Voltage needed for eMarkers!
SPI1 MOSI/I2S1
(SPI1/I2S1) OUT
ADC_IN2 (WKUP4)
If CC not connected through, then we must have an internal Rp 56k or Rd 5.1k resistor (legacy cable marking). If not -> error
BOOT0 internally pulled low
BOOT0 High + Reset -> Enter Bootloader to flash Firmware BOOT0 Low + Reset -> Run Program from Flash
(ADC_IN7) OUT
(SPI1 MOSI/I2S1, WKUP6) OUT
USB-C PD 2 DB CC2
ADC_IN4
Close JP5 1-2 & JP6 2-3 for standard connection of RST / BOOT Close JP5 2-3 & JP6 1-2 for inverted connection of RST / BOOT
Tag-Connect TC2050-IDC statt SWD IDC socket? (costly...)
USB-C PD 2 CC2
(SPI2 MISO) IN
ADC_IN1
(ADC_IN15) OUT
CC Lines on ADC inputs to check for Ra / Continuity. To do that, pull one CC line high (output pullup) and check on other CC pins if high or not. For Ra / VCONN check, pull other (not CC) pin high via Input Pullup and check if pin is low (if so -> Ra present in cable)
USB-C PD 1 CC1
USART RX
RM0444 Design Manual Sec. 38.4.6: If dead battery behavior is not required (for example for source only products), then UCPDx_DBCC1 and UCPDx_DBCC2 pins must both be tied to ground.
USB-C PD 1 DB CC2
(ADC_IN9) OUT
(ADC_IN10) OUT
OSC OUT
SWDIO internally pulled high
LDO reicht wahrscheinlich, Buck ist overkill
OSC32 OUT (avoid)
Jumpers to be able to pull B Side high if it does not read high correctly if pulled high by connected cable from A Side. If these jumpers are set to 2-3, it could be necessary to replace RN1-3 with lower-value resistor arrays.
(SPI2 SCK) OUT
1.8V to 6.5V
USB-C PD 2 FRSTX
Device
AN5096 Sec. 5.6: Unused I/O pins should not be left floating. They should be connected t oa fixed logic level of 0 or 1 by an external or internal pull-up or pull-down. The other option is to configure GPIO as output mode using software. Unused features should be frozen or disabled, wich is their d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
(SPI2 SCK) IN
Nucleo adds an external 100k resistor to the SWCLK/BOOT0 pin. Do I need them?
USB-C PD 2 DB CC1
Prevent backfeeding while SWD is connected
USB-C PD 2 CC1
(ADC_IN8) OUT

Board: 4 copper layers, 150 parts (130 on the bottom side), 205 nets, no tracks yet.

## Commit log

2025-07-10 Update README.md
    Added link to Reddit
2025-07-10 Changed Schematic to white bg colour
2025-08-03 Added project files and license and updated schematic pdf
2025-08-03 Updated license
